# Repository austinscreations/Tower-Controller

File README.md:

# Tower Controller
# formerly mini-notification-tower

I've recently found good sellers for lower cost industrial towers, while I'll still 3d print my own 180 degree tower light and share files should someone want to build one, I've now designed a semi-universal controller for controlling analog 12-24v tower lights

New code can be found here: [Github](https://github.com/austinscreations/OXRS-AC-TowerController-ESP8266-FW) <br>
Load up a bin file in wifi or ethernet mode and provision the device using the admin UI: [Github](https://github.com/OXRS-IO/OXRS-IO-AdminUI-WEB-APP) <br>
Compatable with the (http://oxrs.io) system

As someone who has a home office and a workshop in the garage I wanted an easy way to have notifications whereever I am.
traditional 5 layer led notification lights are large and pricey.
I set out to make a smaller alternative solution. with 3d printing I made a 180 degree light, with the help of a 3d printed mold I was able to use epoxy resin and tints to create the lenses.

-

Red - flashing - immediate issue (such as a fire alarm or CO alarm)

Red - machine error (cnc or 3d printer)

Yellow - flashing - machine error / require attention (such as a 3d printer filament sensor or 3d print ends)

Yellow - equipement On - temperature related (3d printer active (hot end or heat bed) or soldering iron on)

Green - equipment on but idle (say 3d printer or soldering iron is on but not running a job

Blue - notifications (with the help of an I2C lcd I'm able to show messages

White - tied to my doorbell (one to my office door and front house door)

-

Version 1 used 5mm leds in a 3d printed insert - mosfets controlelr wired to 5v and arduino nano. the arduino nano was linked to an rf433 reciever for the doorbell.

Version 2 will include a PCB for a Wemos d1 mini and SMD leds, and I want to try to make a 360 degree model as well.
          
RF433 will be offloaded to a esp-01 to build a seprate gateway for my home assitant installation.

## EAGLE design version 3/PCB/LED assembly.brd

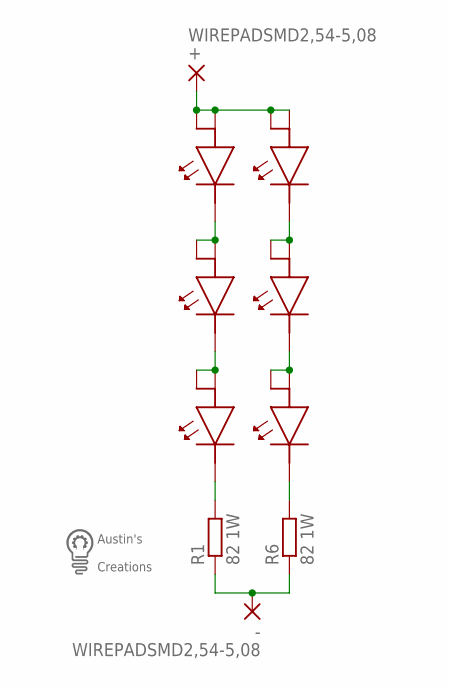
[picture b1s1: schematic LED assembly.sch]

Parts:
+: WIREPADSMD2,54-5,08; SMD2,54-5,08
-: WIREPADSMD2,54-5,08; SMD2,54-5,08
R1, R6: 82 1W; R2010
U$1: LOGOMED
U$6, U$7, U$8, U$23, U$24, U$25: 5730LED

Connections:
N: U$6.P$2, U$7.P$1, U$7.P$3
unnamed: -.1, R1.1, R6.1
unnamed: U$7.P$2, U$8.P$1, U$8.P$3
unnamed: R1.2, U$8.P$2
unnamed: U$23.P$2, U$24.P$1, U$24.P$3
unnamed: U$24.P$2, U$25.P$1, U$25.P$3
unnamed: R6.2, U$25.P$2
VIN: +.1, U$6.P$1, U$6.P$3, U$23.P$1, U$23.P$3

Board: 2 copper layers, 11 parts (0 on the bottom side), 8 nets, no tracks yet.

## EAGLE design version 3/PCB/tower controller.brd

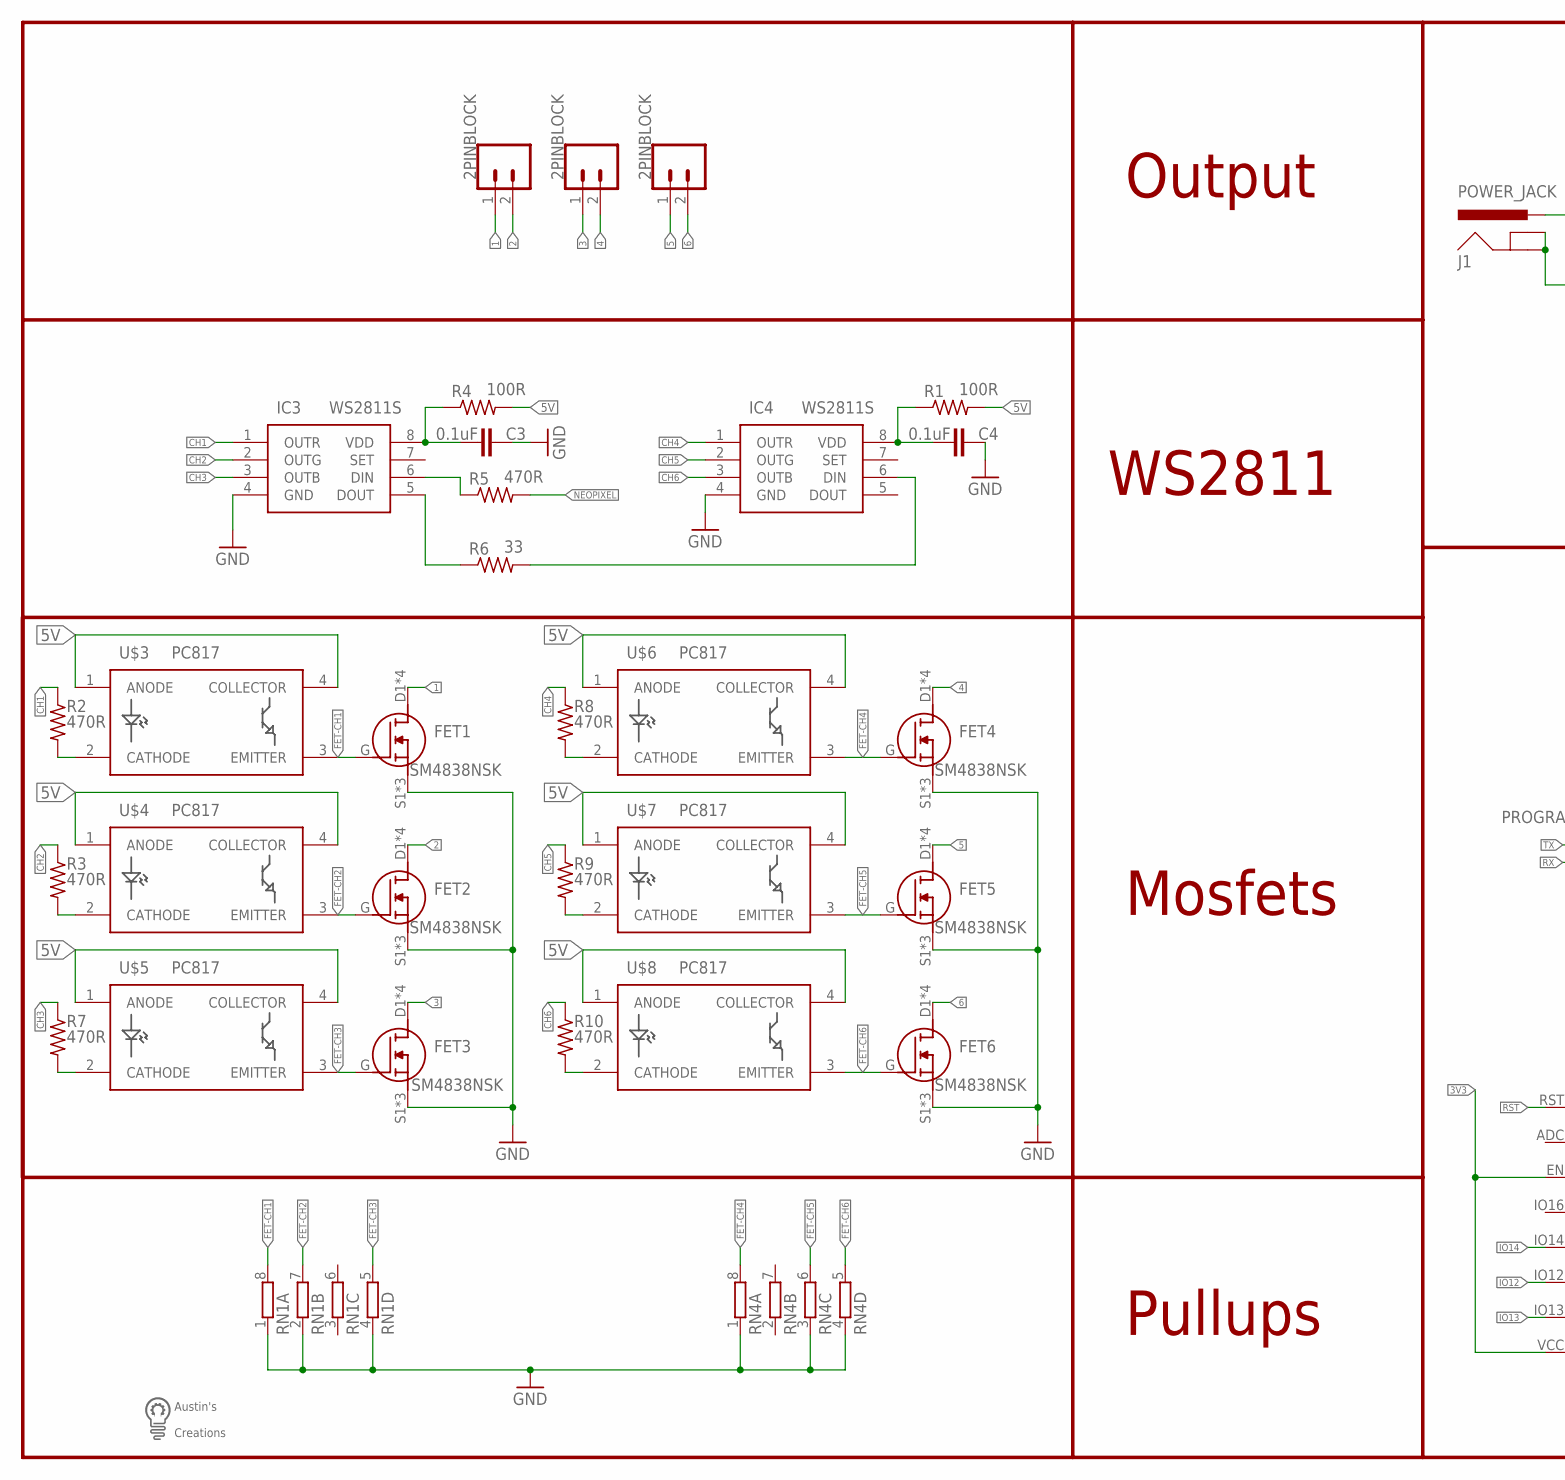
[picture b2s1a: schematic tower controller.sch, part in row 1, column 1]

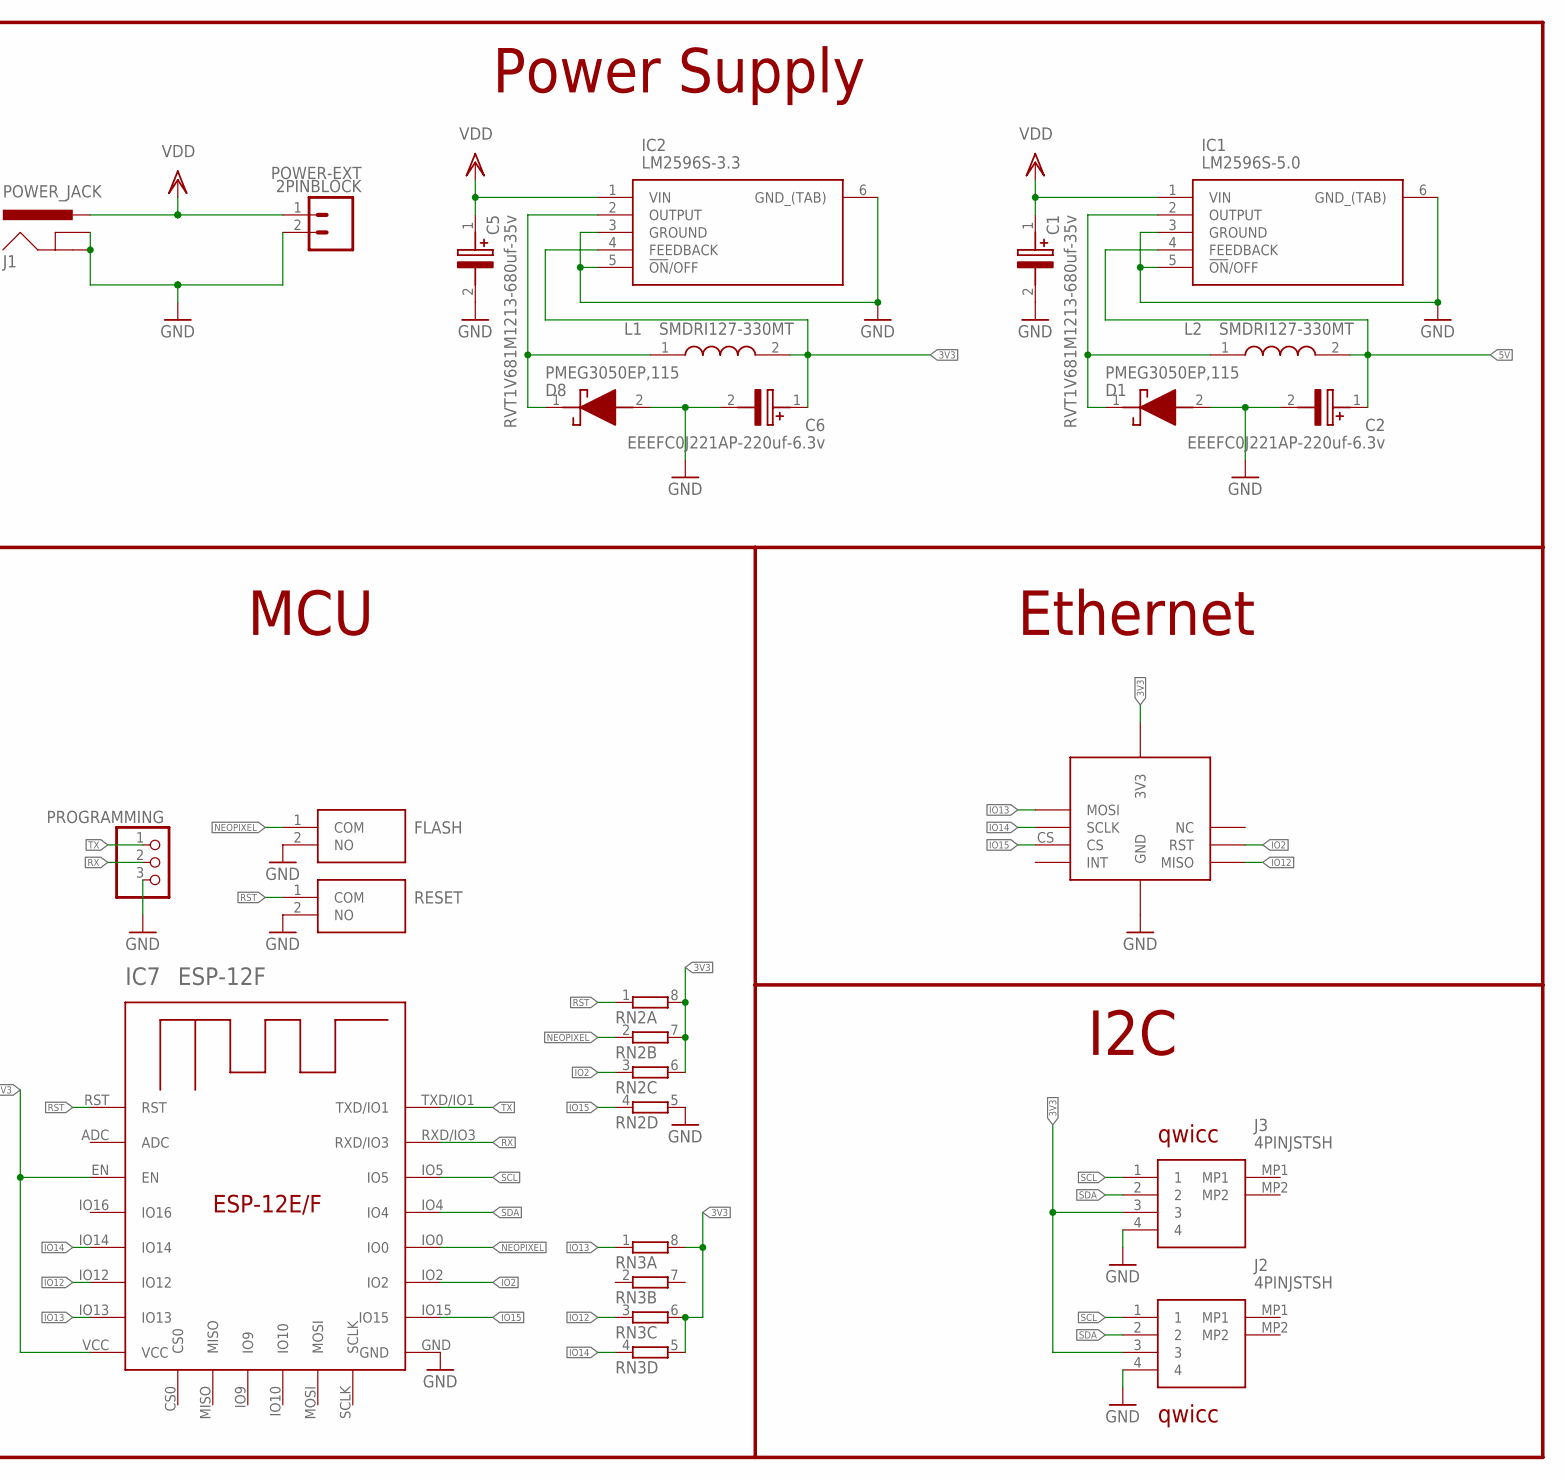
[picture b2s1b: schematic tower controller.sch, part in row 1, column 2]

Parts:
C1, C5: RVT1V681M1213-680uf-35v; CAPAE1350X1400N
C2, C6: EEEFC0J221AP-220uf-6.3v; CAPAE830X650N
C3, C4: 0.1uF; C0603
D1, D8: PMEG3050EP,115; PMEG3050EP115
FET1, FET2, FET3, FET4, FET5, FET6: SM4838NSK
FLASH: PTS636_SM25F_SMTR_LFS; PTS636SM25FSMTRLFS
GND, GND10, GND11: 2PINBLOCK; SCREWTERMINAL-5MM-2
IC1: LM2596S-5.0; TO170P1435X465-6N
IC2: LM2596S-3.3; TO170P1435X465-6N
IC3, IC4: WS2811S; SOIC127P600X175-8N
IC7: ESP-12F; ESP-12E
J1: POWER_JACK; POWER_JACK_PTH
J2, J3: 4PINJSTSH; 665104131822
L1, L2: SMDRI127-330MT; INDPM120120X800N
POWER-EXT: 2PINBLOCK; SCREWTERMINAL-5MM-2
PROGRAMMING: PINHD-1X3; 1X03
R1, R4: 100R; R0603
R2, R3, R5, R7, R8, R9, R10: 470R; R0603
R6: 33; R0603
RESET: PTS636_SM25F_SMTR_LFS; PTS636SM25FSMTRLFS
RN1, RN2, RN3, RN4: 4R-N0603-ARC; 0603-ARC
U$1: W5500MODULE
U$2: LOGOMED
U$3, U$4, U$5, U$6, U$7, U$8: PC817; SOP254P960X420-4N

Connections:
1: FET1.D1 (D), FET1.D2 (D), FET1.D3 (D), FET1.D4 (D), GND.1
2: FET2.D1 (D), FET2.D2 (D), FET2.D3 (D), FET2.D4 (D), GND.2
3: FET3.D1 (D), FET3.D2 (D), FET3.D3 (D), FET3.D4 (D), GND10.1
3V3: C6.1 (+), IC2.4 (FEEDBACK), IC7.EN, IC7.VCC, J2.3, J3.3, L1.2, RN2.6 (2), RN2.7 (2), RN2.8 (2), RN3.5 (2), RN3.6 (2), RN3.8 (2), U$1.3V3_1 (3V3), U$1.3V3_2 (3V3)
4: FET4.D1 (D), FET4.D2 (D), FET4.D3 (D), FET4.D4 (D), GND10.2
5: FET5.D1 (D), FET5.D2 (D), FET5.D3 (D), FET5.D4 (D), GND11.1
5V: C2.1 (+), IC1.4 (FEEDBACK), L2.2, R1.2, R4.2, U$3.1 (ANODE), U$3.4 (COLLECTOR), U$4.1 (ANODE), U$4.4 (COLLECTOR), U$5.1 (ANODE), U$5.4 (COLLECTOR), U$6.1 (ANODE), U$6.4 (COLLECTOR), U$7.1 (ANODE), U$7.4 (COLLECTOR), U$8.1 (ANODE), U$8.4 (COLLECTOR)
6: FET6.D1 (D), FET6.D2 (D), FET6.D3 (D), FET6.D4 (D), GND11.2
CH1: IC3.1 (OUTR), R2.1
CH2: IC3.2 (OUTG), R3.1
CH3: IC3.3 (OUTB), R7.1
CH4: IC4.1 (OUTR), R8.1
CH5: IC4.2 (OUTG), R9.1
CH6: IC4.3 (OUTB), R10.1
FET-CH1: FET1.G, RN1.8 (2), U$3.3 (EMITTER)
FET-CH2: FET2.G, RN1.7 (2), U$4.3 (EMITTER)
FET-CH3: FET3.G, RN1.5 (2), U$5.3 (EMITTER)
FET-CH4: FET4.G, RN4.8 (2), U$6.3 (EMITTER)
FET-CH5: FET5.G, RN4.6 (2), U$7.3 (EMITTER)
FET-CH6: FET6.G, RN4.5 (2), U$8.3 (EMITTER)
GND: C1.2 (-), C2.2 (-), C3.1, C4.1, C5.2 (-), C6.2 (-), D1.2 (A), D8.2 (A), FET1.S1 (S), FET1.S2 (S), FET1.S3 (S), FET2.S1 (S), FET2.S2 (S), FET2.S3 (S), FET3.S1 (S), FET3.S2 (S), FET3.S3 (S), FET4.S1 (S), FET4.S2 (S), FET4.S3 (S), FET5.S1 (S), FET5.S2 (S), FET5.S3 (S), FET6.S1 (S), FET6.S2 (S), FET6.S3 (S), FLASH.2 (NO), IC1.3 (GROUND), IC1.5 (!ON!/OFF), IC1.6 (GND_(TAB)), IC2.3 (GROUND), IC2.5 (!ON!/OFF), IC2.6 (GND_(TAB)), IC3.4 (GND), IC4.4 (GND), IC7.GND, J1.GND, J1.GNDBREAK, J2.4, J3.4, POWER-EXT.2, PROGRAMMING.3, RESET.2 (NO), RN1.1, RN1.2 (1), RN1.4 (1), RN2.5 (2), RN4.1, RN4.3 (1), RN4.4 (1), U$1.GND1 (GND), U$1.GND2 (GND), U$1.GND3 (GND)
IO2: IC7.IO2, RN2.3 (1), U$1.RST
IO12: IC7.IO12, RN3.3 (1), U$1.MISO
IO13: IC7.IO13, RN3.1, U$1.MOSI
IO14: IC7.IO14, RN3.4 (1), U$1.SCLK
IO15: IC7.IO15, RN2.4 (1), U$1.CS
unnamed: D1.1 (K), IC1.2 (OUTPUT), L2.1
unnamed: C4.2, IC4.8 (VDD), R1.1
unnamed: IC4.6 (DIN), R6.2
unnamed: C3.2, IC3.8 (VDD), R4.1
unnamed: IC3.6 (DIN), R5.1
unnamed: IC3.5 (DOUT), R6.1
unnamed: R3.2, U$4.2 (CATHODE)
unnamed: R2.2, U$3.2 (CATHODE)
unnamed: R7.2, U$5.2 (CATHODE)
unnamed: R8.2, U$6.2 (CATHODE)
unnamed: R9.2, U$7.2 (CATHODE)
unnamed: R10.2, U$8.2 (CATHODE)
unnamed: D8.1 (K), IC2.2 (OUTPUT), L1.1
NEOPIXEL: FLASH.1 (COM), IC7.IO0, R5.2, RN2.2 (1)
RST: IC7.RST, RESET.1 (COM), RN2.1
RX: IC7.RXD/IO3, PROGRAMMING.2
SCL: IC7.IO5, J2.1, J3.1
SDA: IC7.IO4, J2.2, J3.2
TX: IC7.TXD/IO1, PROGRAMMING.1
VDD: C1.1 (+), C5.1 (+), IC1.1 (VIN), IC2.1 (VIN), J1.PWR, POWER-EXT.1

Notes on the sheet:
qwicc
MCU
Power Supply
Ethernet
I2C
WS2811
Mosfets
Output
Pullups

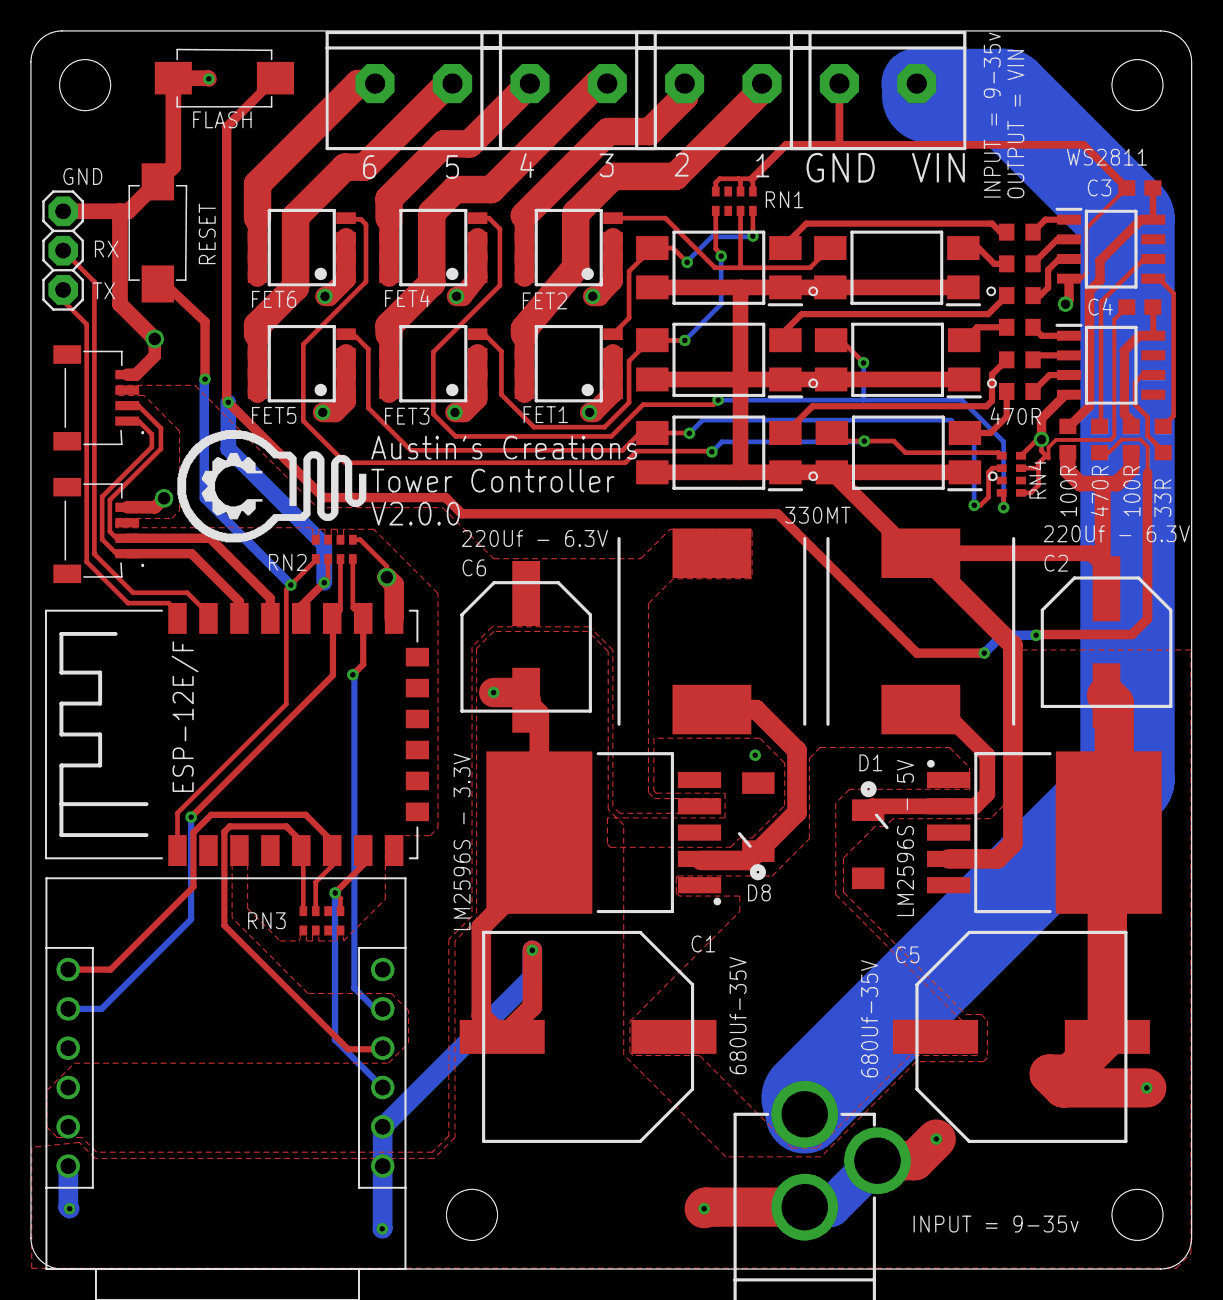
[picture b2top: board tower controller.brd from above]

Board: 2 copper layers, 75.0 x 80.0 mm, 53 parts (0 on the bottom side), 46 nets.

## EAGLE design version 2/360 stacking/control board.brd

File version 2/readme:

Version 2 

This version has the tower assembly using 5730 LEd's for lighting and a spot on the pcb for a wemos D1 mini.

***this version is larger than the v1 so taht both the 180 degree and 360 degree assebbilies can be the same size.***

Requires 12v power to run - diode proetcting 5v regualtor when programming via usb

will be updated as I create the PCB files, code and 3d housings will be made and adjusted once I order parts for assembly and testing.

2020-12-12
updated control board pcb in version 2 stacking edition
added intial 3d model photo of teh 3d printable model that will be used to assemble the lights

2020-12-04
added photos of the pcb designs of each version
added cost breakdown in main version 22 folder for each version. doesn't include 3d printed parts / power supply - using ebay canada as source

2020-12-03:
Created new files. there are different assemblies. 

180 version = has a single led panel with wemos d1 mini - giving ~180 degree ilumination

360 stacking = used a control board and led boards - using brass stand offs to conenct each baord. there are solder jumpers which are to be used to route the signal
for the ws2811s chip that controls the led mosfets. the depending on led color you need 82 ohm or 39 ohm 2010 1 watt resistors (text on pcb). 
each baord will allow you to program 3 segment animations on the led baord. 3d printed parts with 45 degree angles nad chrome paint can be used to redirect light.

360 version = uses 4 straight led panels to connect to a control board via 90 degree headers. uses ws2811s chip to control LED mosfets

Boards are currently untested and don't have 3d assembly files, working on multiple projects and home to do a mass ebay order to fill parts on these projects to keep my costs down.

Hope to expore the option of a POE powered and ethernet controlled tower

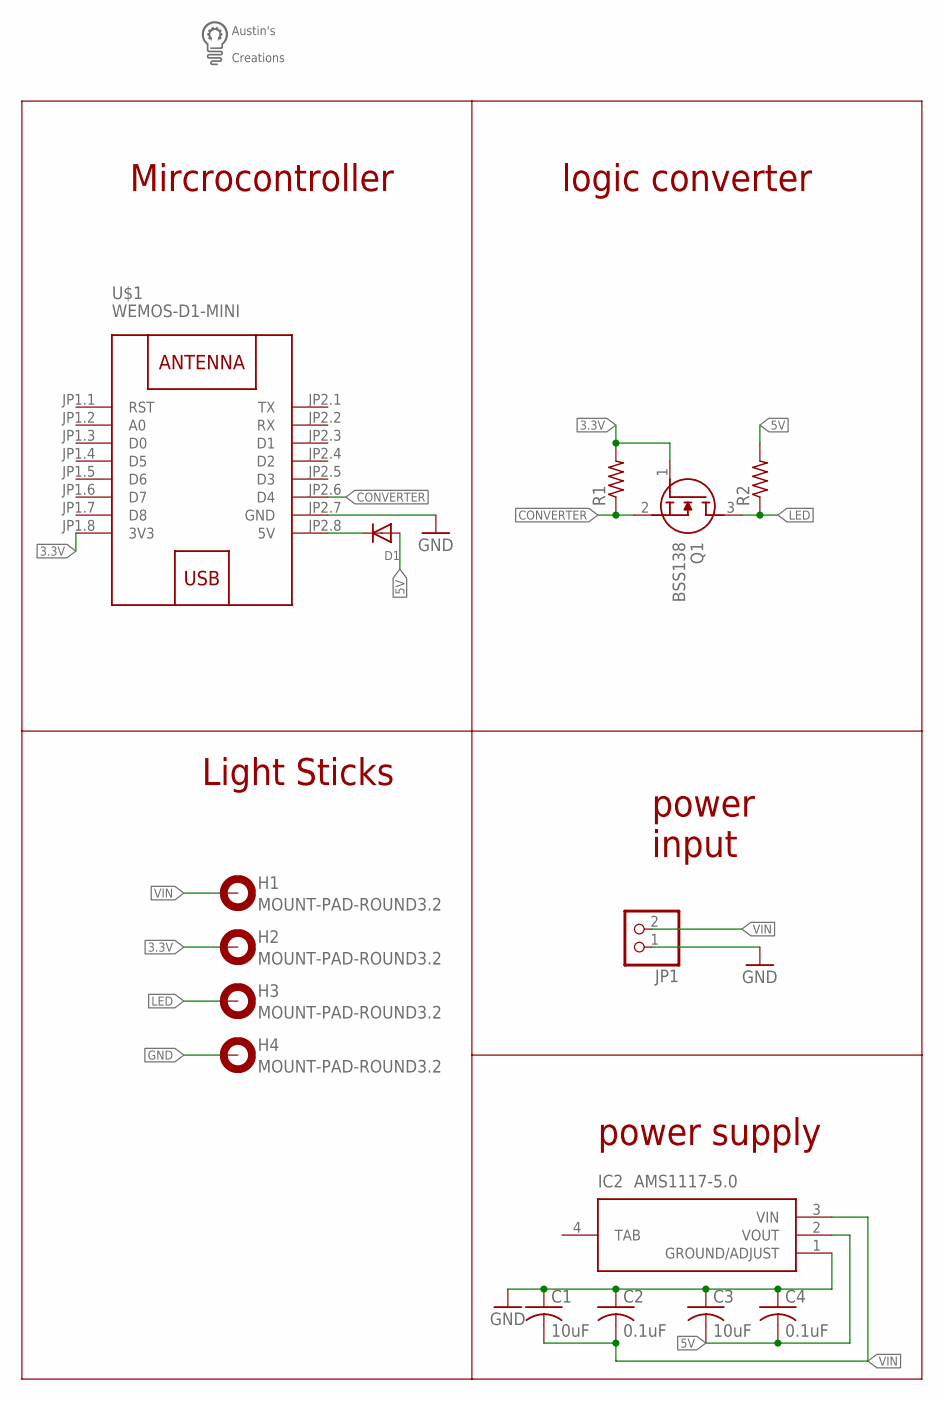
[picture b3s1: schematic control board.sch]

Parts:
C1, C3: 10uF; C0603
C2, C4: 0.1uF; C0603
D1: DIODESOD-123; SOD-123
H1, H2, H3, H4: MOUNT-PAD-ROUND3.2; 3,2-PAD
IC2: AMS1117-5.0; SOT229P700X180-4N
JP1: PINHD-1X2; 1X02
Q1: BSS138; SOT95P240X120-3N
R1, R2: R-US_R0603; R0603
U$1: WEMOS-D1-MINI
U$2: LOGO

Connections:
3.3V: H2.B3,2, Q1.1 (G), R1.2, U$1.JP1.8 (3V3)
5V: C3.2, C4.2, D1.A, IC2.2 (VOUT), R2.2
CONVERTER: Q1.2 (S), R1.1, U$1.JP2.6 (D4)
GND: C1.1, C2.1, C3.1, C4.1, H4.B3,2, IC2.1 (GROUND/ADJUST), JP1.1, U$1.JP2.7 (GND)
LED: H3.B3,2, Q1.3 (D), R2.1
unnamed: D1.C, U$1.JP2.8 (5V)
VIN: C1.2, C2.2, H1.B3,2, IC2.3 (VIN), JP1.2

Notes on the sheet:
Light Sticks
power supply
power input
Mircrocontroller
logic converter

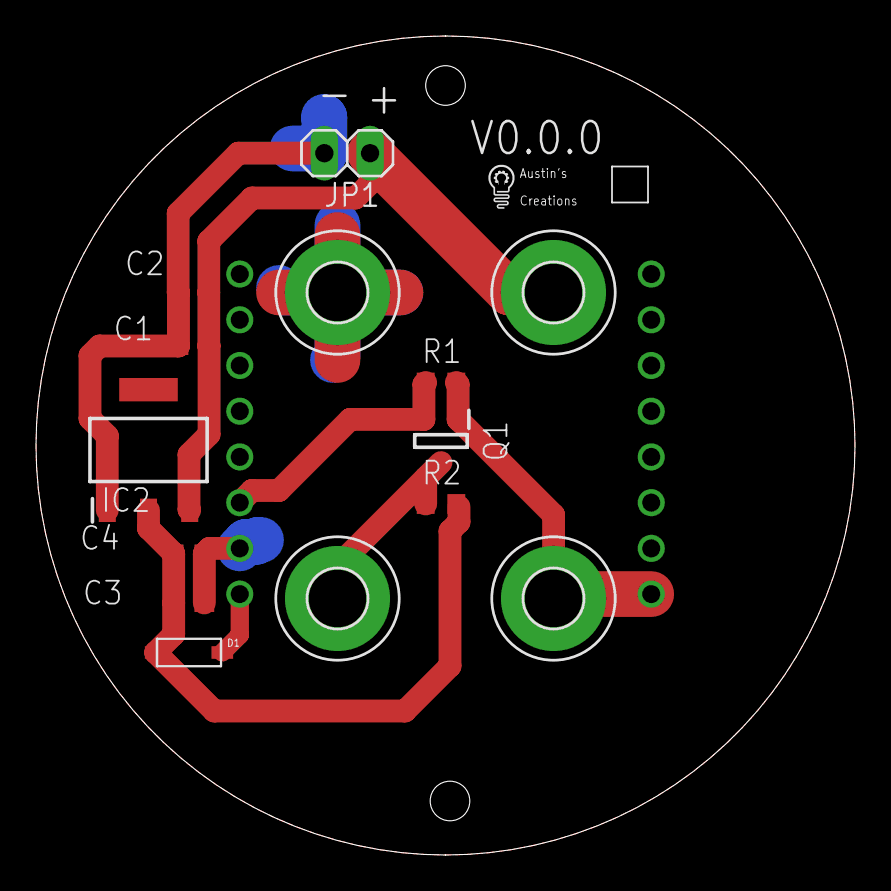
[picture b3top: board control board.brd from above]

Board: 2 copper layers, 45.5 x 45.5 mm, 16 parts (1 on the bottom side), 7 nets.

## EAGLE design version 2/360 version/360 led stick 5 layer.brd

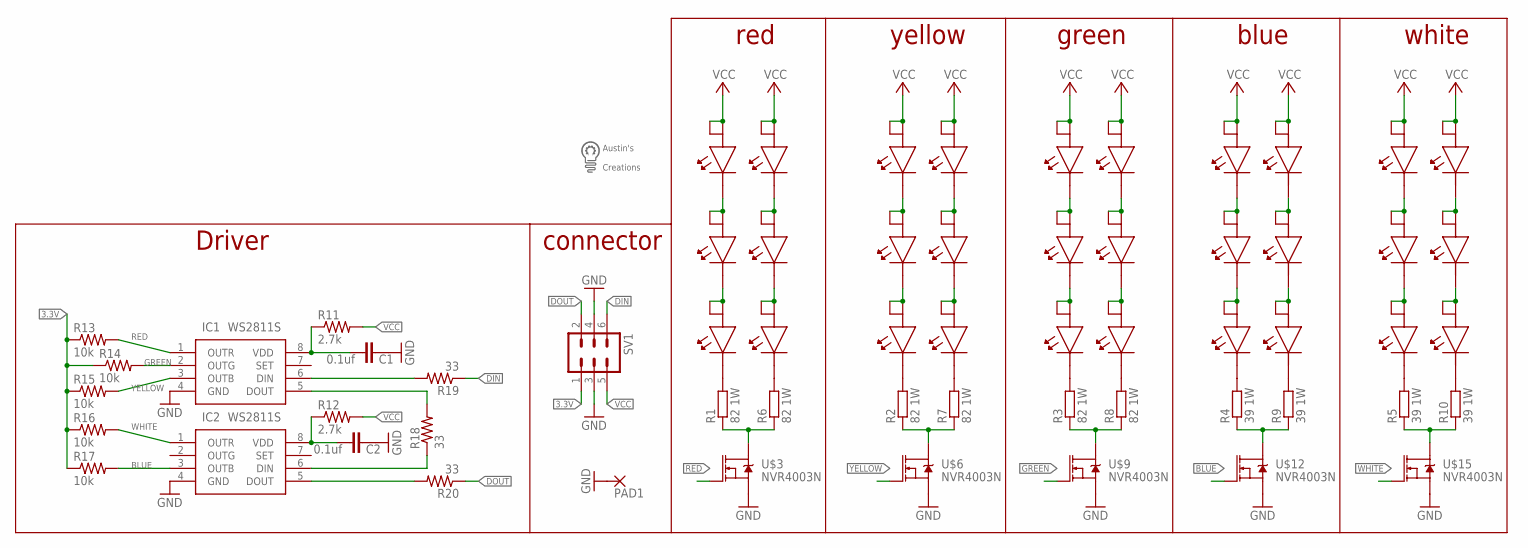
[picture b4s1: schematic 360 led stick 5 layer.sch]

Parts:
C1, C2: 0.1uf; C0603K
IC1, IC2: WS2811S; SOIC127P600X175-8N
PAD1: WIREPADSMD1,27-254; SMD1,27-2,54
R1, R2, R3, R6, R7, R8: 82 1W; R1210
R4, R5, R9, R10: 39 1W; R1210
R11, R12: 2.7k; R0603
R13, R14, R15, R16, R17: 10k; R0603
R18, R19, R20: 33; R0603
SV1: MA03-2
U$1, U$2, U$4, U$5, U$7, U$8, U$10, U$11, U$13, U$14, U$16, U$17, U$18, U$19, U$20, U$22, U$23, U$24, U$25, U$26, U$27, U$28, U$29, U$30, U$31, U$32, U$33, U$34, U$35, U$36: 5730LED
U$3, U$6, U$9, U$12, U$15: NVR4003N; SOT23
U$21: LOGO

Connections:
3.3V: R13.1, R14.1, R15.1, R16.1, R17.1, SV1.1
BLUE: IC2.3 (OUTB), R17.2, U$12.2 (G)
DIN: R19.1, SV1.6
DOUT: R20.1, SV1.2
GND: C1.1, C2.1, IC1.4 (GND), IC2.4 (GND), PAD1.1, SV1.3, SV1.4, U$3.3 (S), U$6.3 (S), U$9.3 (S), U$12.3 (S), U$15.3 (S)
GREEN: IC1.2 (OUTG), R14.2, U$9.2 (G)
unnamed: U$1.P$2, U$2.P$1, U$2.P$3
unnamed: U$2.P$2, U$4.P$1, U$4.P$3
unnamed: R1.2, U$4.P$2
unnamed: U$5.P$2, U$7.P$1, U$7.P$3
unnamed: U$7.P$2, U$8.P$1, U$8.P$3
unnamed: R2.2, U$8.P$2
unnamed: U$10.P$2, U$11.P$1, U$11.P$3
unnamed: U$11.P$2, U$13.P$1, U$13.P$3
unnamed: R3.2, U$13.P$2
unnamed: U$14.P$2, U$16.P$1, U$16.P$3
unnamed: U$16.P$2, U$17.P$1, U$17.P$3
unnamed: R4.2, U$17.P$2
unnamed: U$18.P$2, U$19.P$1, U$19.P$3
unnamed: U$19.P$2, U$20.P$1, U$20.P$3
unnamed: R5.2, U$20.P$2
unnamed: R1.1, R6.1, U$3.1 (D)
unnamed: R2.1, R7.1, U$6.1 (D)
unnamed: R3.1, R8.1, U$9.1 (D)
unnamed: R4.1, R9.1, U$12.1 (D)
unnamed: R5.1, R10.1, U$15.1 (D)
unnamed: U$22.P$2, U$23.P$1, U$23.P$3
unnamed: U$23.P$2, U$24.P$1, U$24.P$3
unnamed: R6.2, U$24.P$2
unnamed: U$25.P$2, U$26.P$1, U$26.P$3
unnamed: U$26.P$2, U$27.P$1, U$27.P$3
unnamed: R7.2, U$27.P$2
unnamed: U$28.P$2, U$29.P$1, U$29.P$3
unnamed: U$29.P$2, U$30.P$1, U$30.P$3
unnamed: R8.2, U$30.P$2
unnamed: U$31.P$2, U$32.P$1, U$32.P$3
unnamed: U$32.P$2, U$33.P$1, U$33.P$3
unnamed: R9.2, U$33.P$2
unnamed: U$34.P$2, U$35.P$1, U$35.P$3
unnamed: U$35.P$2, U$36.P$1, U$36.P$3
unnamed: R10.2, U$36.P$2
unnamed: C1.2, IC1.8 (VDD), R11.1
unnamed: IC1.6 (DIN), R19.2
unnamed: IC2.6 (DIN), R18.1
unnamed: C2.2, IC2.8 (VDD), R12.1
unnamed: IC1.5 (DOUT), R18.2
unnamed: IC2.5 (DOUT), R20.2
RED: IC1.1 (OUTR), R13.2, U$3.2 (G)
VCC: R11.2, R12.2, SV1.5, U$1.P$1, U$1.P$3, U$5.P$1, U$5.P$3, U$10.P$1, U$10.P$3, U$14.P$1, U$14.P$3, U$18.P$1, U$18.P$3, U$22.P$1, U$22.P$3, U$25.P$1, U$25.P$3, U$28.P$1, U$28.P$3, U$31.P$1, U$31.P$3, U$34.P$1, U$34.P$3
WHITE: IC2.1 (OUTR), R16.2, U$15.2 (G)
YELLOW: IC1.3 (OUTB), R15.2, U$6.2 (G)

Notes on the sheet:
red
yellow
green
blue
white
connector
Driver

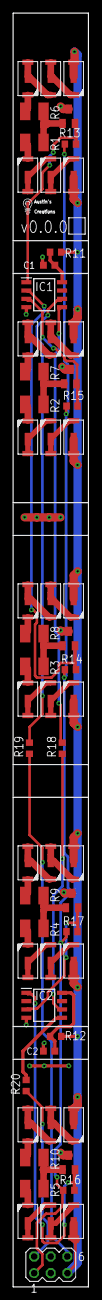
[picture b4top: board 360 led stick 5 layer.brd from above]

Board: 2 copper layers, 11.5 x 194.5 mm, 62 parts (1 on the bottom side), 51 nets.

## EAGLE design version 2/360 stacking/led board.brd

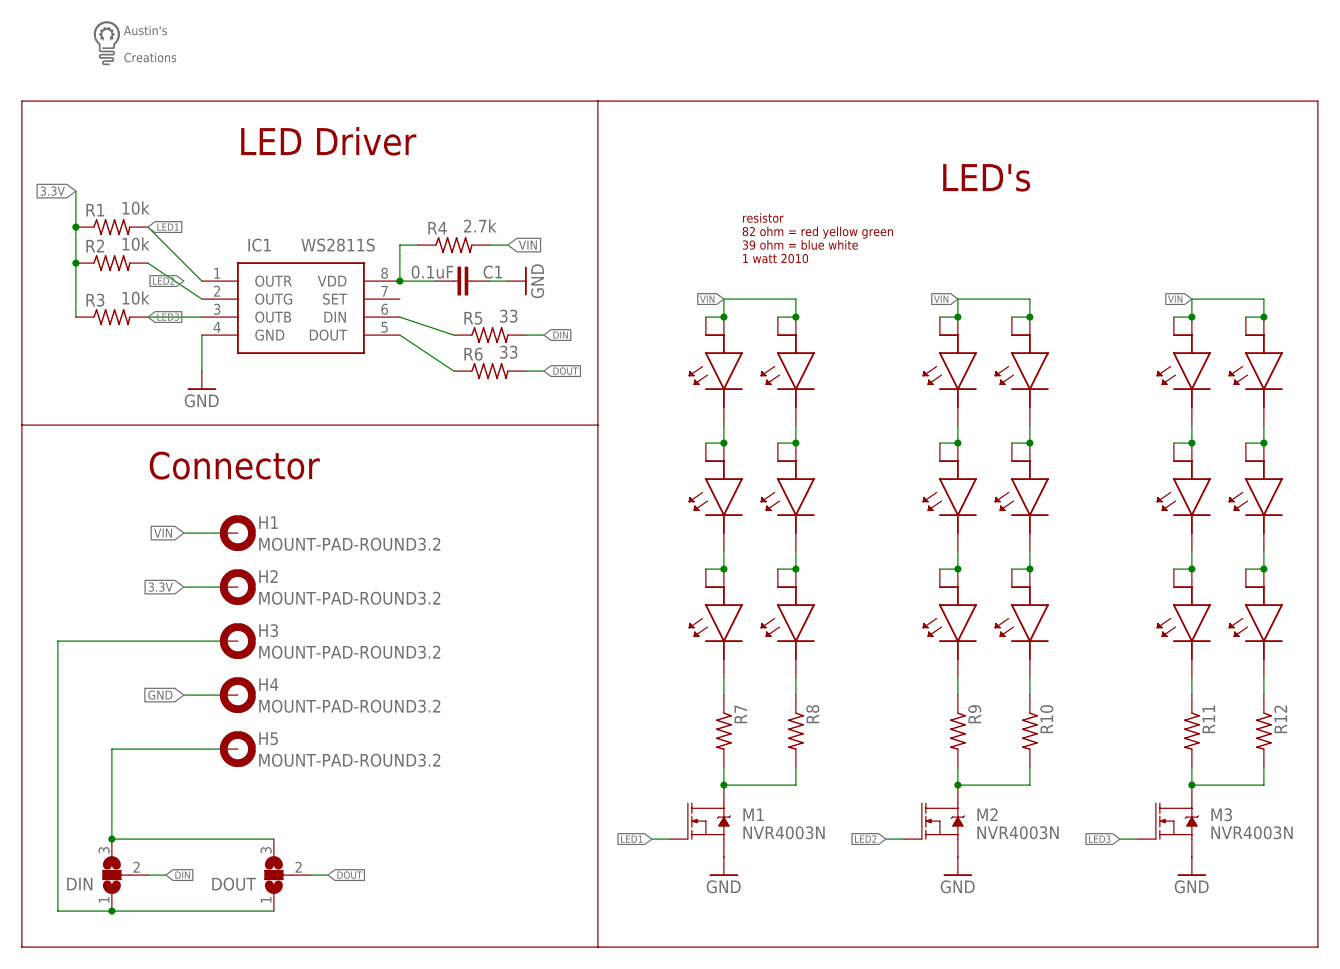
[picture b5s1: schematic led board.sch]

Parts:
C1: 0.1uF; C0603K
DIN: SJ2WW; SJ_2W
DOUT: SJ2WW; SJ_2W
H1, H2, H3, H4, H5: MOUNT-PAD-ROUND3.2; 3,2-PAD
IC1: WS2811S; SOIC127P600X175-8N
L1, L2, L3, L4, L5, L6, L7, L8, L9, L10, L11, L12, L13, L14, L15, L16, L17, L18: 5730LED
M1, M2, M3: NVR4003N; SOT23
R1, R2, R3: 10k; R0603
R4: 2.7k; R0603
R5, R6: 33; R0603
R7, R8, R9, R10, R11, R12: R-US_R2010; R2010
U$2: LOGO

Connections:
3.3V: H2.B3,2, R1.1, R2.1, R3.1
DIN: DIN.2, R5.2
DOUT: DOUT.2, R6.2
GND: C1.1, H4.B3,2, IC1.4 (GND), M1.3 (S), M2.3 (S), M3.3 (S)
LED1: IC1.1 (OUTR), M1.2 (G), R1.2
LED2: IC1.2 (OUTG), M2.2 (G), R2.2
LED3: IC1.3 (OUTB), M3.2 (G), R3.2
unnamed: DIN.3, DOUT.3, H5.B3,2
unnamed: DIN.1, DOUT.1, H3.B3,2
unnamed: L3.P$2, R7.1
unnamed: C1.2, IC1.8 (VDD), R4.1
unnamed: IC1.6 (DIN), R5.1
unnamed: IC1.5 (DOUT), R6.1
unnamed: L2.P$2, L3.P$1, L3.P$3
unnamed: L1.P$2, L2.P$1, L2.P$3
unnamed: M1.1 (D), R7.2, R8.2
unnamed: L6.P$2, R8.1
unnamed: L5.P$2, L6.P$1, L6.P$3
unnamed: L4.P$2, L5.P$1, L5.P$3
unnamed: L9.P$2, R9.1
unnamed: L8.P$2, L9.P$1, L9.P$3
unnamed: L7.P$2, L8.P$1, L8.P$3
unnamed: M2.1 (D), R9.2, R10.2
unnamed: L12.P$2, R10.1
unnamed: L11.P$2, L12.P$1, L12.P$3
unnamed: L10.P$2, L11.P$1, L11.P$3
unnamed: L15.P$2, R11.1
unnamed: L14.P$2, L15.P$1, L15.P$3
unnamed: L13.P$2, L14.P$1, L14.P$3
unnamed: M3.1 (D), R11.2, R12.2
unnamed: L18.P$2, R12.1
unnamed: L17.P$2, L18.P$1, L18.P$3
unnamed: L16.P$2, L17.P$1, L17.P$3
VIN: H1.B3,2, L1.P$1, L1.P$3, L4.P$1, L4.P$3, L7.P$1, L7.P$3, L10.P$1, L10.P$3, L13.P$1, L13.P$3, L16.P$1, L16.P$3, R4.2

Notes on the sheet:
Connector
resistor 82 ohm = red yellow green 39 ohm = blue white 1 watt 2010
LED Driver
LED's

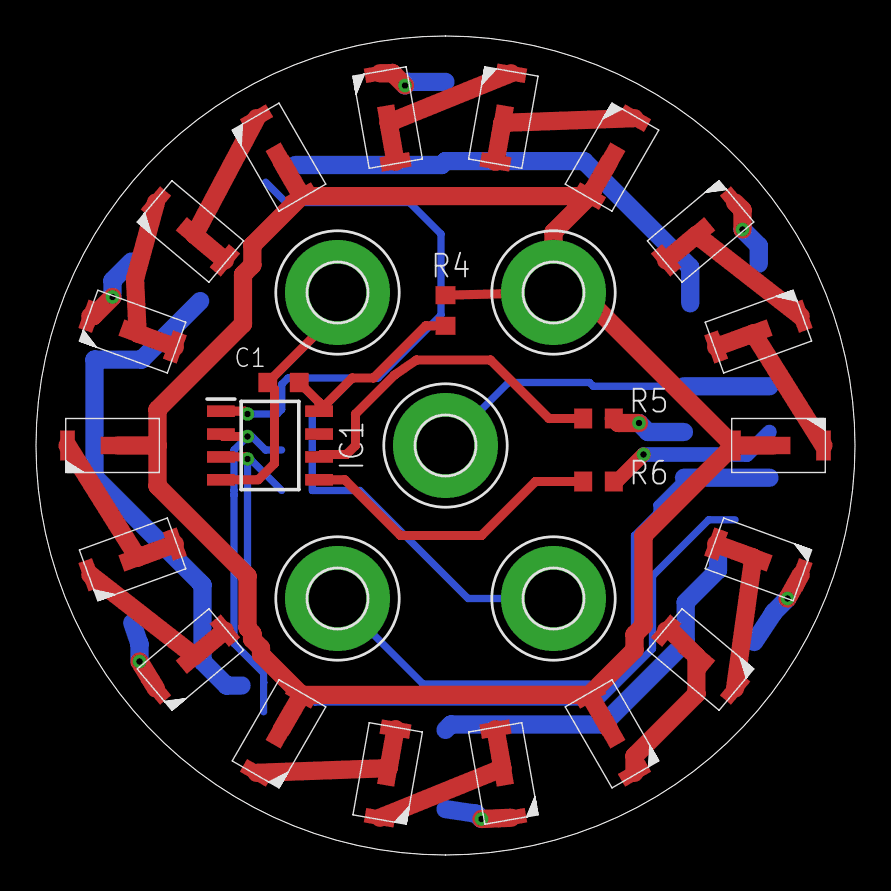
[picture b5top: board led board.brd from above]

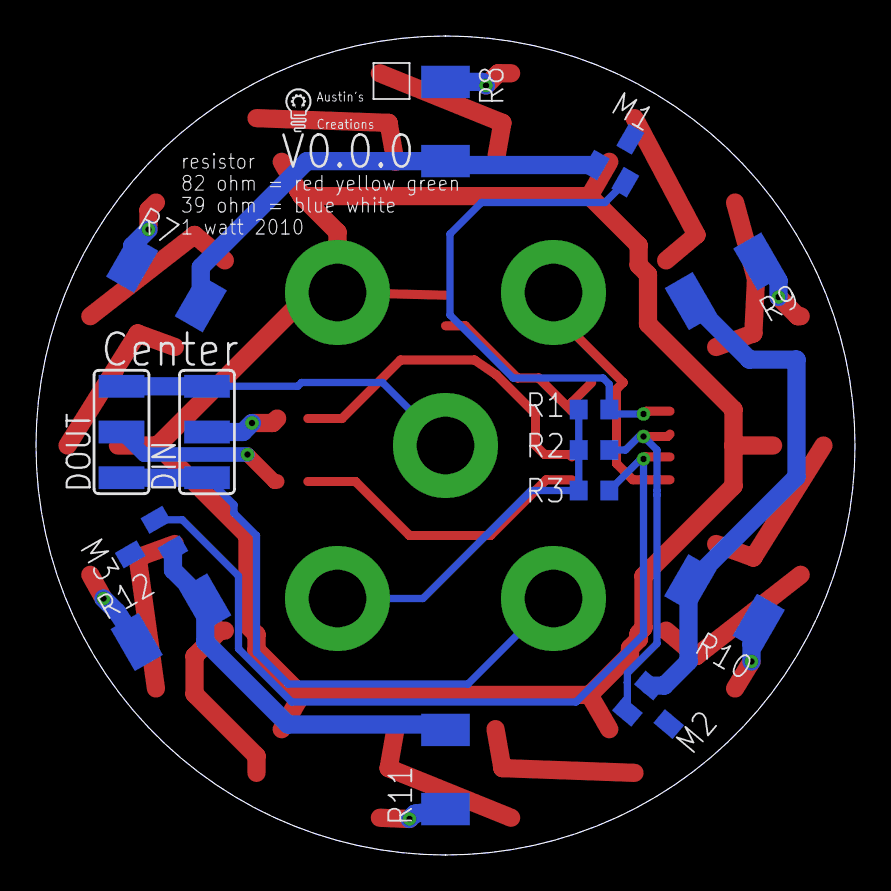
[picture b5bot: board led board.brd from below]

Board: 2 copper layers, 45.5 x 45.5 mm, 43 parts (15 on the bottom side), 34 nets.

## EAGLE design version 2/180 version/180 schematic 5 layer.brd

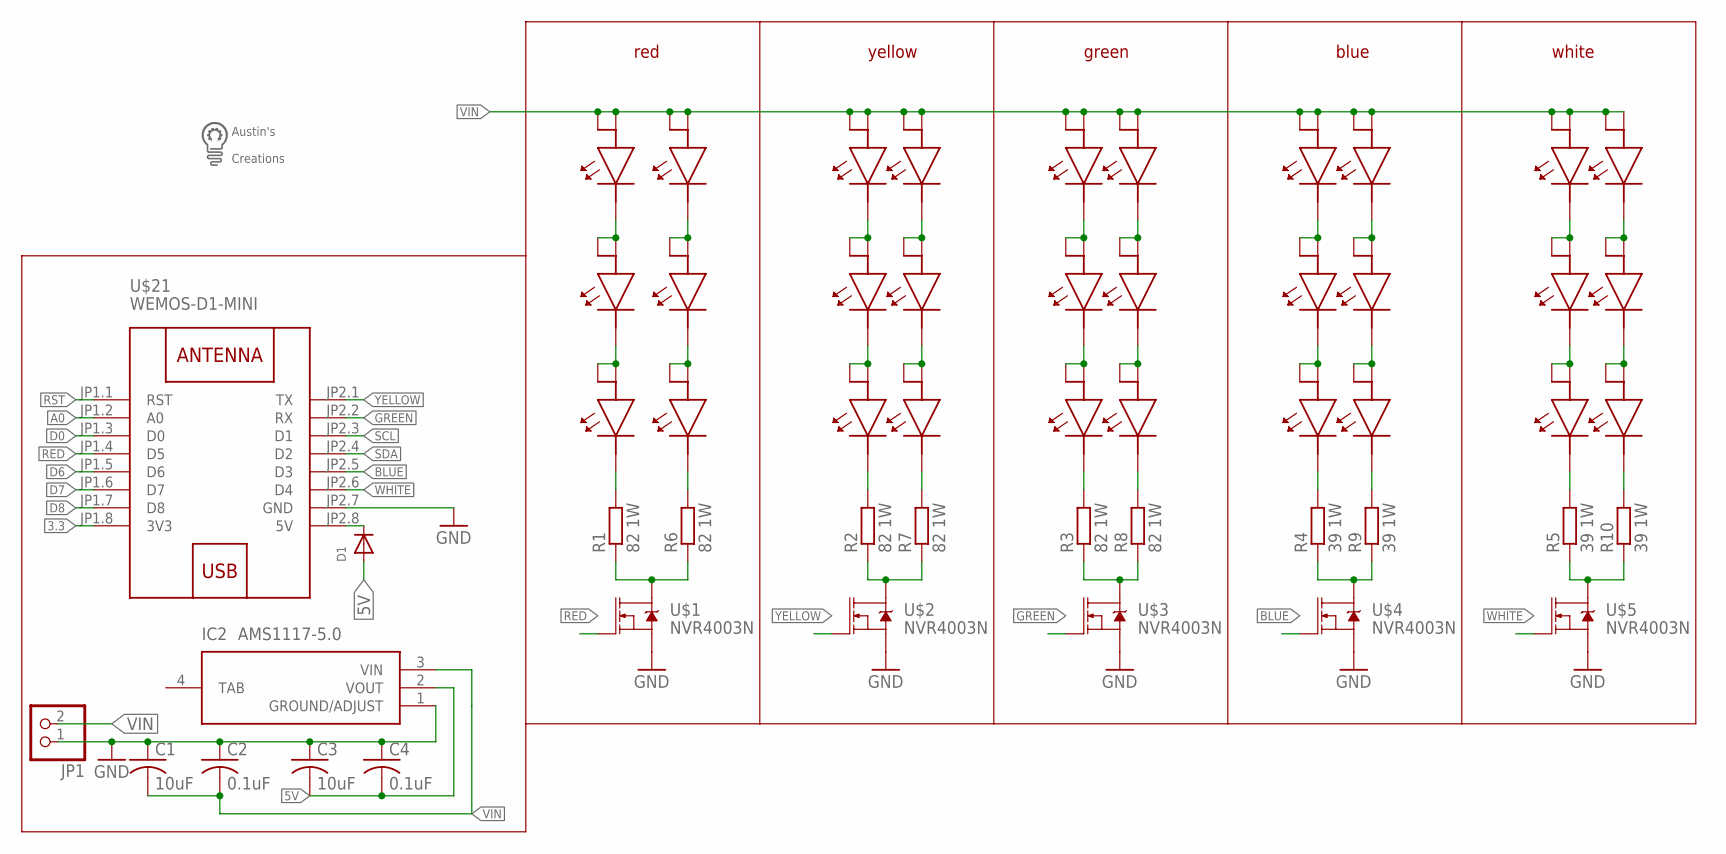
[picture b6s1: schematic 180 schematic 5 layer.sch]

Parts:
C1, C3: 10uF; C0603
C2, C4: 0.1uF; C0603
D1: DIODESOD-123; SOD-123
IC2: AMS1117-5.0; SOT229P700X180-4N
JP1: PINHD-1X2; 1X02
R1, R2, R3, R6, R7, R8: 82 1W; R2010
R4, R5, R9, R10: 39 1W; R2010
U$1, U$2, U$3, U$4, U$5: NVR4003N; SOT23
U$6, U$7, U$8, U$9, U$10, U$11, U$12, U$13, U$14, U$15, U$16, U$17, U$18, U$19, U$20, U$23, U$24, U$25, U$26, U$27, U$28, U$29, U$30, U$31, U$32, U$33, U$34, U$35, U$36, U$37: 5730LED
U$21: WEMOS-D1-MINI
U$22: LOGO

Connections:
3.3: U$21.JP1.8 (3V3)
5V: C3.2, C4.2, D1.A, IC2.2 (VOUT)
A0: U$21.JP1.2 (A0)
BLUE: U$4.2 (G), U$21.JP2.5 (D3)
D0: U$21.JP1.3 (D0)
D6: U$21.JP1.5 (D6)
D7: U$21.JP1.6 (D7)
D8: U$21.JP1.7 (D8)
GND: C1.1, C2.1, C3.1, C4.1, IC2.1 (GROUND/ADJUST), JP1.1, U$1.3 (S), U$2.3 (S), U$3.3 (S), U$4.3 (S), U$5.3 (S), U$21.JP2.7 (GND)
GREEN: U$3.2 (G), U$21.JP2.2 (RX)
unnamed: D1.C, U$21.JP2.8 (5V)
unnamed: U$6.P$2, U$7.P$1, U$7.P$3
unnamed: U$9.P$2, U$10.P$1, U$10.P$3
unnamed: R1.1, R6.1, U$1.1 (D)
unnamed: R2.1, R7.1, U$2.1 (D)
unnamed: U$12.P$2, U$13.P$1, U$13.P$3
unnamed: U$15.P$2, U$16.P$1, U$16.P$3
unnamed: U$18.P$2, U$19.P$1, U$19.P$3
unnamed: U$7.P$2, U$8.P$1, U$8.P$3
unnamed: R1.2, U$8.P$2
unnamed: R2.2, U$11.P$2
unnamed: R3.2, U$14.P$2
unnamed: R4.2, U$17.P$2
unnamed: R5.2, U$20.P$2
unnamed: U$19.P$2, U$20.P$1, U$20.P$3
unnamed: U$16.P$2, U$17.P$1, U$17.P$3
unnamed: U$13.P$2, U$14.P$1, U$14.P$3
unnamed: U$10.P$2, U$11.P$1, U$11.P$3
unnamed: U$23.P$2, U$24.P$1, U$24.P$3
unnamed: U$24.P$2, U$25.P$1, U$25.P$3
unnamed: R3.1, R8.1, U$3.1 (D)
unnamed: R4.1, R9.1, U$4.1 (D)
unnamed: R5.1, R10.1, U$5.1 (D)
unnamed: R6.2, U$25.P$2
unnamed: U$29.P$2, U$30.P$1, U$30.P$3
unnamed: U$26.P$2, U$27.P$1, U$27.P$3
unnamed: R7.2, U$28.P$2
unnamed: U$27.P$2, U$28.P$1, U$28.P$3
unnamed: R8.2, U$31.P$2
unnamed: U$30.P$2, U$31.P$1, U$31.P$3
unnamed: U$32.P$2, U$33.P$1, U$33.P$3
unnamed: R9.2, U$34.P$2
unnamed: U$33.P$2, U$34.P$1, U$34.P$3
unnamed: U$35.P$2, U$36.P$1, U$36.P$3
unnamed: R10.2, U$37.P$2
unnamed: U$36.P$2, U$37.P$1, U$37.P$3
RED: U$1.2 (G), U$21.JP1.4 (D5)
RST: U$21.JP1.1 (RST)
SCL: U$21.JP2.3 (D1)
SDA: U$21.JP2.4 (D2)
VIN: C1.2, C2.2, IC2.3 (VIN), JP1.2, U$6.P$1, U$6.P$3, U$9.P$1, U$9.P$3, U$12.P$1, U$12.P$3, U$15.P$1, U$15.P$3, U$18.P$1, U$18.P$3, U$23.P$1, U$23.P$3, U$26.P$1, U$26.P$3, U$29.P$1, U$29.P$3, U$32.P$1, U$32.P$3, U$35.P$1, U$35.P$3
WHITE: U$5.2 (G), U$21.JP2.6 (D4)
YELLOW: U$2.2 (G), U$21.JP2.1 (TX)

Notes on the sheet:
red
yellow
green
blue
white

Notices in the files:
parts and their libraries:
diy-modules: Released under the Creative Commons Attribution 4.0 International License: http://creativecommons.org/licenses/by/4.0
